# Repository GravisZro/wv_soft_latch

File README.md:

# Wide Voltage Soft Latch
This simple circuit is designed to be a safe (low current) way of activating a battery-based circuit for up to 100V.  A momentary switch connecting the `Switch` pin to `GND` activates the circuit.

# Details
* Minimalistic: only 7 components
* Connects directly to a battery
* Intended to turn on volatage regulator (up to 1A) for an MCU
* `Enable` pin connects to an MCU to allow for the circuit to deactivate itself

# Notes
1. The circuit relies on an MCU to pull the `Enable` pin low, therefore to ensure proper operation, during initalization the MCU should...
  * Check if the MCU was reset by the watchdog timer (AVR uses an `MCUCSR` flag) and pull the `Enable` pin either high or low, depending on the state.
  * Set the MCU's watchdog timer which will automatically reset the MCU (and thus turn off the circuit) if your code gets stuck.
2. Cheap 0.1" pins typically max out at 3A and 100V, so if you modify this for current exceeding 3A or voltage exceeding 100V then either integrate it into your circuit or select pins carefully.

# Schematic

# PCB

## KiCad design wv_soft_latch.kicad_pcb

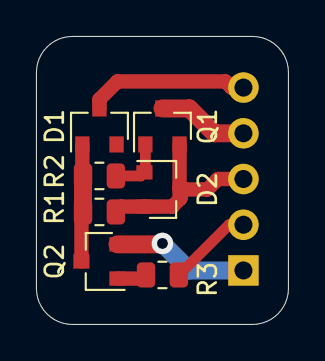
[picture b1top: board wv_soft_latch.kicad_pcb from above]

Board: 2 copper layers, 14.0 x 16.0 mm, 8 parts (1 on the bottom side), 8 nets.

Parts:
D1: 100V; D_SOT-23_ANK
D2: BZX84-C10; D_SOT-23_ANK
J1: Conn_01x05; PinHeader_1x05_P2.54mm_Vertical
Q1: SI01P10; SOT-23
Q2: MMBT5551L; SOT-23
R1, R3: 100kΩ; R_0805_2012Metric
R2: 1MΩ; R_0805_2012Metric

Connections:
/Soft latch/Enable: J1.2, R3.1
/Soft latch/GND: J1.1, Q2.2
/Soft latch/Switch-GND: D1.1, J1.5
/Soft latch/Vin: D2.1, J1.3, Q1.2, R1.1
/Soft latch/Vout: J1.4, Q1.3
unnamed: D1.2, Q2.3, R1.2, R2.1
unnamed: D2.2, Q1.1, R2.2
unnamed: Q2.1, R3.2

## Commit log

2021-10-03 initial upload
